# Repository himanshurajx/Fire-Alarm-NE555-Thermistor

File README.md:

## 🔥 Fire Alarm using Thermistor and 555 Timer

This project demonstrates a heat-activated alarm using an **NTC thermistor** and the **NE555 timer IC**. When the temperature near the sensor rises, the buzzer starts beeping. Designed as a beginner-friendly electronics project, this helped enhance my hands-on skills in analog circuits, sensor interfacing, and timer-based design.

---

## 🔧 Tools & Technologies Used

- **NE555 Timer IC** – Makes the beeping signal
- **NTC Thermistor (10K)** – Senses heat (resistance drops as temperature rises)
- **BC547 Transistor** – Switches the 555 timer on and off based on temperature
- **Potentiometers (RV1 10K, RV2 100K)** – RV1 sets the trigger temperature, RV2 sets the beep speed
- **Active Buzzer** – Makes the alarm sound
- **9V Battery** – Powers the circuit
- **Autodesk EAGLE** – Used to design the schematic and the PCB layout
- **Resistors, capacitors, switch, wires** – Supporting parts

---

## 🧾 Parts List

| Part | Value | Use |
|------|-------|-----|
| B1 | 9V battery | Power |
| S1 | Switch | On/off |
| IC1 | NE555 | Oscillator |
| Q1 | BC547 | Switch |
| T1 | 10K NTC thermistor | Heat sensor |
| RV1 | 100K pot | Trigger temperature |
| RV2 | 100K pot | Beep speed |
| R1 | 1K | 555 timing |
| R2 | 46K | Pulls reset pin high |
| R3 | 100K | Base bias for Q1 |
| C | 10µF | 555 timing |
| BUZ1 | Active buzzer | Sound |

---

## 📝 Project Description

- Developed a heat alarm using a thermistor, a transistor and a 555 timer.
- The **thermistor** and **RV1** form a voltage divider that controls the **BC547** transistor.
- The **BC547** controls the reset pin (pin 4) of the **555 timer**.
- The **555** is wired as an oscillator, so the **buzzer** beeps when the alarm is active.
- This project helped me understand basic **sensor interfacing**, **transistor switching** and **555 timer oscillator** design.

---

## 🔌 How It Works

1. When it is cool, the thermistor's resistance is high, so Q1 is **ON** and pulls pin 4 low. The 555 is disabled and the buzzer is silent.
2. When it gets hot, the thermistor's resistance drops, so Q1 turns **OFF**.
3. R3 pulls pin 4 high, the 555 starts, and the buzzer beeps.
4. RV2 changes the beep speed. RV1 changes the temperature at which the alarm starts.

### Setting the trigger temperature

1. Set the desired alarm temperature to **60°C**.
2. For a 10 kΩ NTC thermistor (B = 3950 K), the resistance at 60°C is approximately **2.49 kΩ**.
3. The circuit switching threshold is approximately **8 kΩ**.
4. Set the RV1 potentiometer to approximately **5.5 kΩ** (8 − 2.49 = 5.51 kΩ).
5. Fine-tune RV1 by heating the thermistor and checking the buzzer activation temperature.

---

## 🧠 Learning Outcomes

- Working of NTC thermistors and voltage dividers
- Using a transistor as a switch
- Using the 555 timer as an oscillator
- Power consumption and battery life problems
- Troubleshooting real-world hardware issues

---

## ⚠️ Known Limitations

- It only senses heat close to the sensor. A smoke detector reacts much earlier.
- If the thermistor wire breaks, the alarm stays silent.
- A dead battery gives no warning.
- There is no hysteresis, so the alarm may stutter at the exact trigger temperature.

---

## 🛠️ Design and Implementation

- Designed the circuit schematic and PCB layout using **Autodesk EAGLE**.
- Built and tested the circuit on a breadboard using an NE555 timer, BC547 transistor, NTC thermistor, and buzzer.
- Fabricated the PCB and soldered the components to assemble the final circuit.
- Powered the circuit using a 9V battery.
- Tested the circuit under normal and elevated temperature conditions to verify automatic buzzer activation.
  
---

## 📷 Media

### 🔌 Circuit Diagram:

### 🎥 Demo Video:
👉 [Watch Demo](https://drive.google.com/drive/folders/1Pbn1WBMJVAjlfn9Htr2KEi_Wj8BANrUW?usp=sharing)

---

## 📁 Files

- [Fire_Alarm.sch](Fire_Alarm.sch) – EAGLE schematic
- [Fire_Alarm.brd](Fire_Alarm.brd) – EAGLE board layout

---

## 🔗 Future Improvements

- Make a version 2 of the PCB with the corrected values and the extra parts (series resistor for RV2, bypass capacitors, power switch)
- Make the alarm sound when the thermistor wire breaks (fail-safe)
- Add a low-battery warning
- Add hysteresis so the alarm does not stutter
- Add a smoke sensor along with the heat sensor

---

## 👨‍💻 Author

**Himanshu Raj** |
B.Tech EE @ NIT Patna    
[GitHub](https://github.com/himanshurajx) | [LinkedIn](https://linkedin.com/in/himanshurajx)

---

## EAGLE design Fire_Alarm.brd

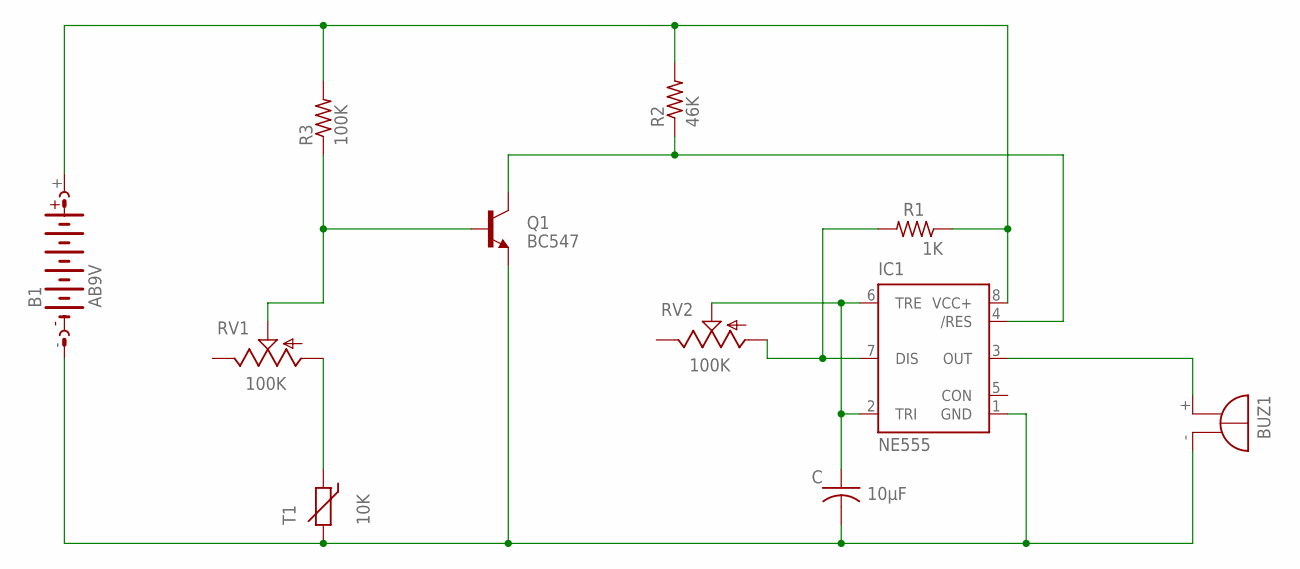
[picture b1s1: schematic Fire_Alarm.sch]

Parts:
B1: AB9V
BUZ1: F/TMB
C: 10μF; C050-024X044
IC1: NE555; DIL-08
Q1: BC547; TO92
R1: 1K; 0204/7
R2: 46K; 0204/7
R3: 100K; 0204/7
RV1, RV2: 100K; CA9V
T1: 10K; R-7,5

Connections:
unnamed: BUZ1.+, IC1.3 (OUT)
unnamed: Q1.2 (B), R3.1, RV1.S
unnamed: RV1.A, T1.1
unnamed: B1.-, BUZ1.-, C.2, IC1.1 (GND), Q1.1 (E), T1.2
unnamed: IC1.4 (/RES), Q1.3 (C), R2.1
unnamed: IC1.7 (DIS), R1.2, RV2.A
unnamed: C.1, IC1.2 (TRI), IC1.6 (TRE), RV2.S
unnamed: B1.+, IC1.8 (VCC+), R1.1, R2.2, R3.2

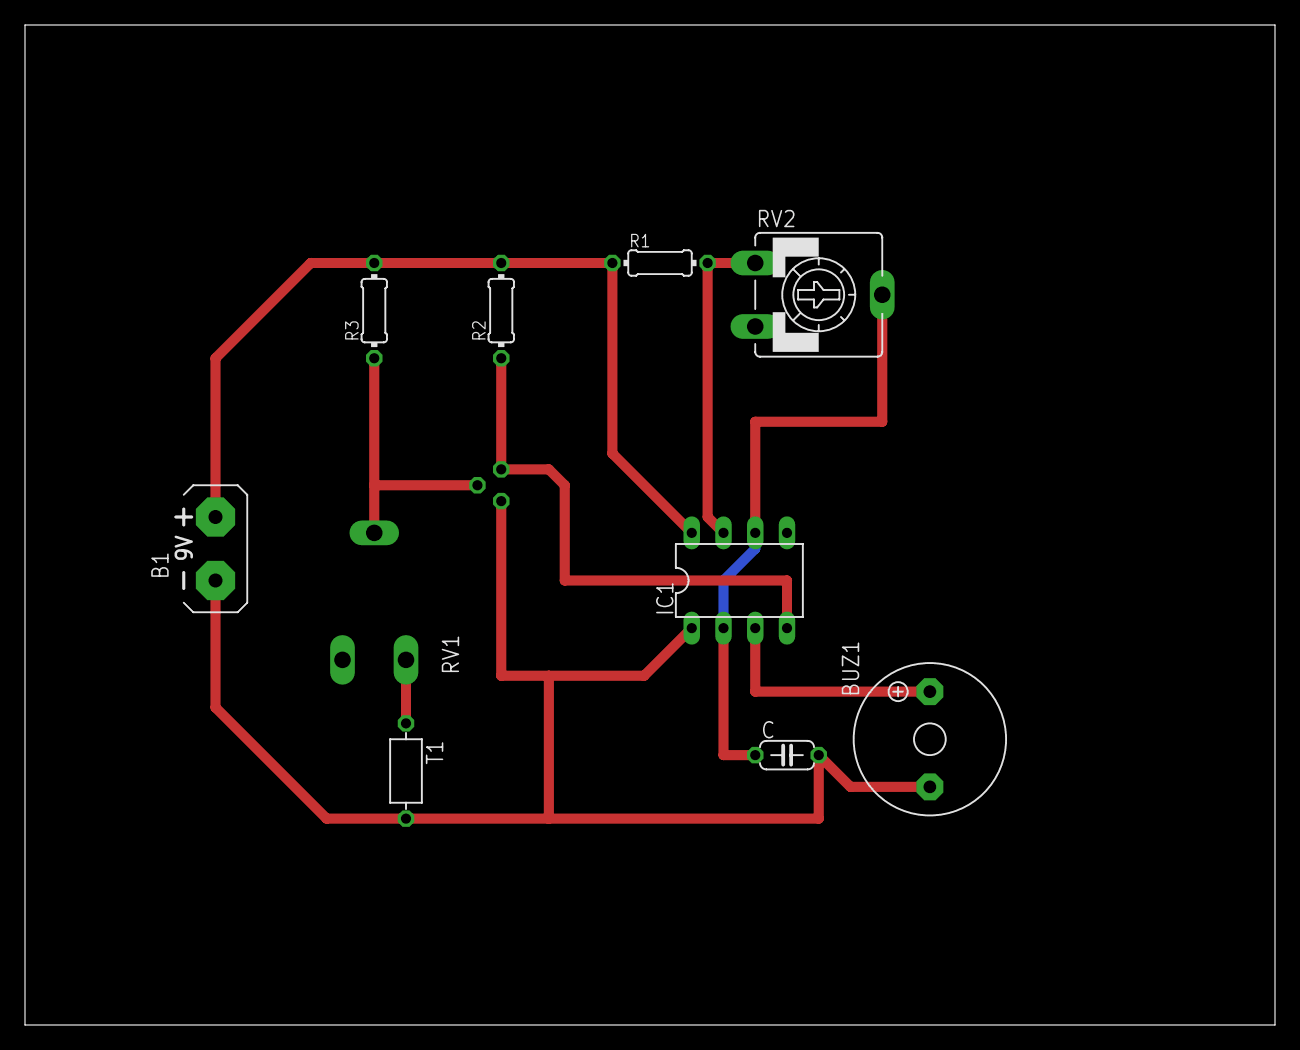
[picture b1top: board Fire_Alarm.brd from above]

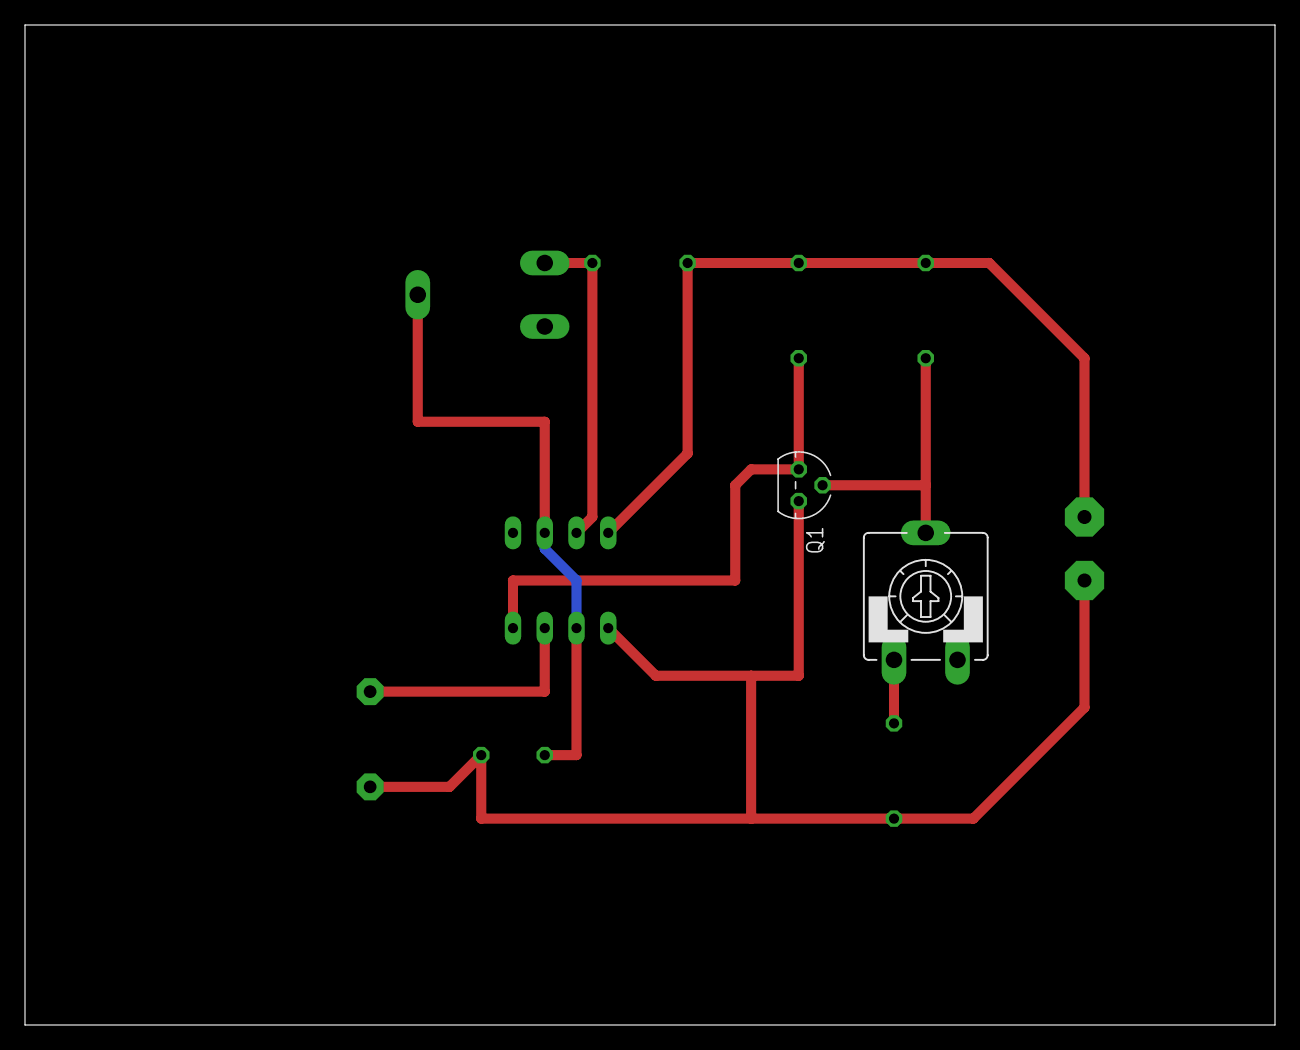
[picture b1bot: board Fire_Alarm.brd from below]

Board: 2 copper layers, 100.0 x 80.0 mm, 11 parts (2 on the bottom side), 8 nets.
